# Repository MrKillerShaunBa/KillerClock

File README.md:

# KillerClock

This is a Nixie tube-inspired clock made using LED filaments. These filaments are strings of micro-LEDs which imitate the look of a tungsten filament. It uses ESP-32, which syncs time with an NTP server using the on-board wifi. It uses a MAX7219 ic to run the 7 segments. Everything is powered using a 5V 2A wall adaptor. There are also Glass test tubes to match the look of a Nixie tube.

I got the inspiration when I chanced upon a [Nixie tube clock](https://nixieshop.com/), which I found very interesting. Since Nixie tubes aren't available reliably in India, I made one using LEDs.

## CAD

## PCB

# BOM
| Product | Quantity (MOQ) | Source | Total Price(INR)(includes tax) | Price($)(Converted) | Link |
| :-----: | :-----: | :-----: | :-----: | :-----: | :-----: |
| MAX7219 8-Digit LED Display Driver IC | 2 | eBhoot | 225 | 2.60 | [here](https://ebhoot.in/shop-2/ics/driver-interface-ic/max7219-8-digit-led-display-driver-ic/) |
| DC Power Jack Female | 2 | eBhoot | 14.6 | 0.17 | [here](https://ebhoot.in/shop-2/connectors/dc-005-dc-power-jack-female-adapter-pcb-mount-2-1-x-5-5mm/) |
| ESP32 Development Board | 1 | eBhoot | 377.6 | 4.37 | [here](https://ebhoot.in/shop-2/esp-wifi-boards/esp32-development-board-type-c-usb-ch340c-wifi-bluetooth-ultra-low-power-dual-core/) |
| 10uF 25V Electrolytic Capacitor | 3 | eBhoot | 5.31 | 0.061 | [here](https://ebhoot.in/shop-2/electronics-components/capacitors/10uf-25v-electrolytic-capacitor/) |
| 0.1uF Ceramic Capacitor | 5 | eBhoot | 5.3 | 0.061 | [here](https://ebhoot.in/shop-2/electronics-components/capacitors/0-1uf-104-ceramic-capacitor/) |
| 10K Ohm Resistor | 10 | eBhoot | 5.9 | 0.068 | [here](https://ebhoot.in/shop-2/electronics-components/resistors/10k-ohm-0-25watt-carbon-film-resistor/) |
| 5v-2A DC adaptor | 1 | eBhoot | 123.9 | 1.43 | [here](https://ebhoot.in/shop-2/power-supply/adapters/5v-2a-dc-adapter-with-led-dual-pin-dc/) |
| Ebhoot Shipping | ~ | eBhoot | 90 | 1.04 | ~ |
| 40×2 Pin Male Berg Strip | 2 | Sharvi | 28.91 | 0.33 | [here](https://sharvielectronics.com/product/40x2-pin-male-berg-strip-break-away-header-right-angle-2-54mm-pitch/) |
| 40x1 Pin Male Berg Strip | 1 | Sharvi | 6.8 | 0.079 | [here](https://sharvielectronics.com/product/40x1-pin-male-10mm-height-berg-header-straight-2-54mm-pitch/) |
| 40x1 Pin Female Berg Strip | 1 | Sharvi | 9.7 | 0.11 | [here](https://sharvielectronics.com/product/40x1-pin-female-berg-strip-break-away-header-straight-2-54mm-pitch/) |
| 2x4 pin female berg strip | 5 | Sharvi | 49.7 | 0.57 | [here](https://sharvielectronics.com/product/2x4-8pin-female-berg-strip-break-away-header-straight-2-54mm-pitch/) |
| 24 Pin IC Base | 5 | Sharvi | 29.3 | 0.34 | [here](https://sharvielectronics.com/product/24-pin-ic-base-for-dip-24-package/) |
| M2x6mm Allen bolt | 10 | Sharvi | 112.7 | 1.30 | [here](https://sharvielectronics.com/product/m2x6mm-allen-socket-head-cap-bolt-mild-carbon-steel/) |
| M2x20mm Allen Bolt | 10 | Sharvi | 163.5 | 1.89 | [here](https://sharvielectronics.com/product/m2x20mm-allen-socket-head-cap-bolt-mild-carbon-steel/) |
| M2X3mm Brass Heat Insert | 10 | Sharvi | 33.7 | 0.39 | [here](https://sharvielectronics.com/product/m2x3-mm-brass-heat-set-threaded-round-insert-nut/) |
| Sharvi Shipping | ~ | Sharvi | 75 | 0.87 | ~ |
| LED Filament 3V 26mm | 11*3 | Adafruit | ~ | 54.34 | [here](https://www.adafruit.com/product/5505) (Not available in this size anywhere in India; Inclues tax and shipping) |
| 38x200mm test tubes | 12 | Amazon | 990 | 11.45 | [here](https://amzn.in/d/gJka92f) |
| 10x75mm test tubes | 6 | Amazon | 179 | 2.04 | [here](https://amzn.in/d/571r95v) |
| PCB | 5 | JLC PCB | | 20 | Used coupon and includes shipping | 
| Case | 1 | Print Legion | | ~5 | Only Shipping |

Total Cost- $115-120

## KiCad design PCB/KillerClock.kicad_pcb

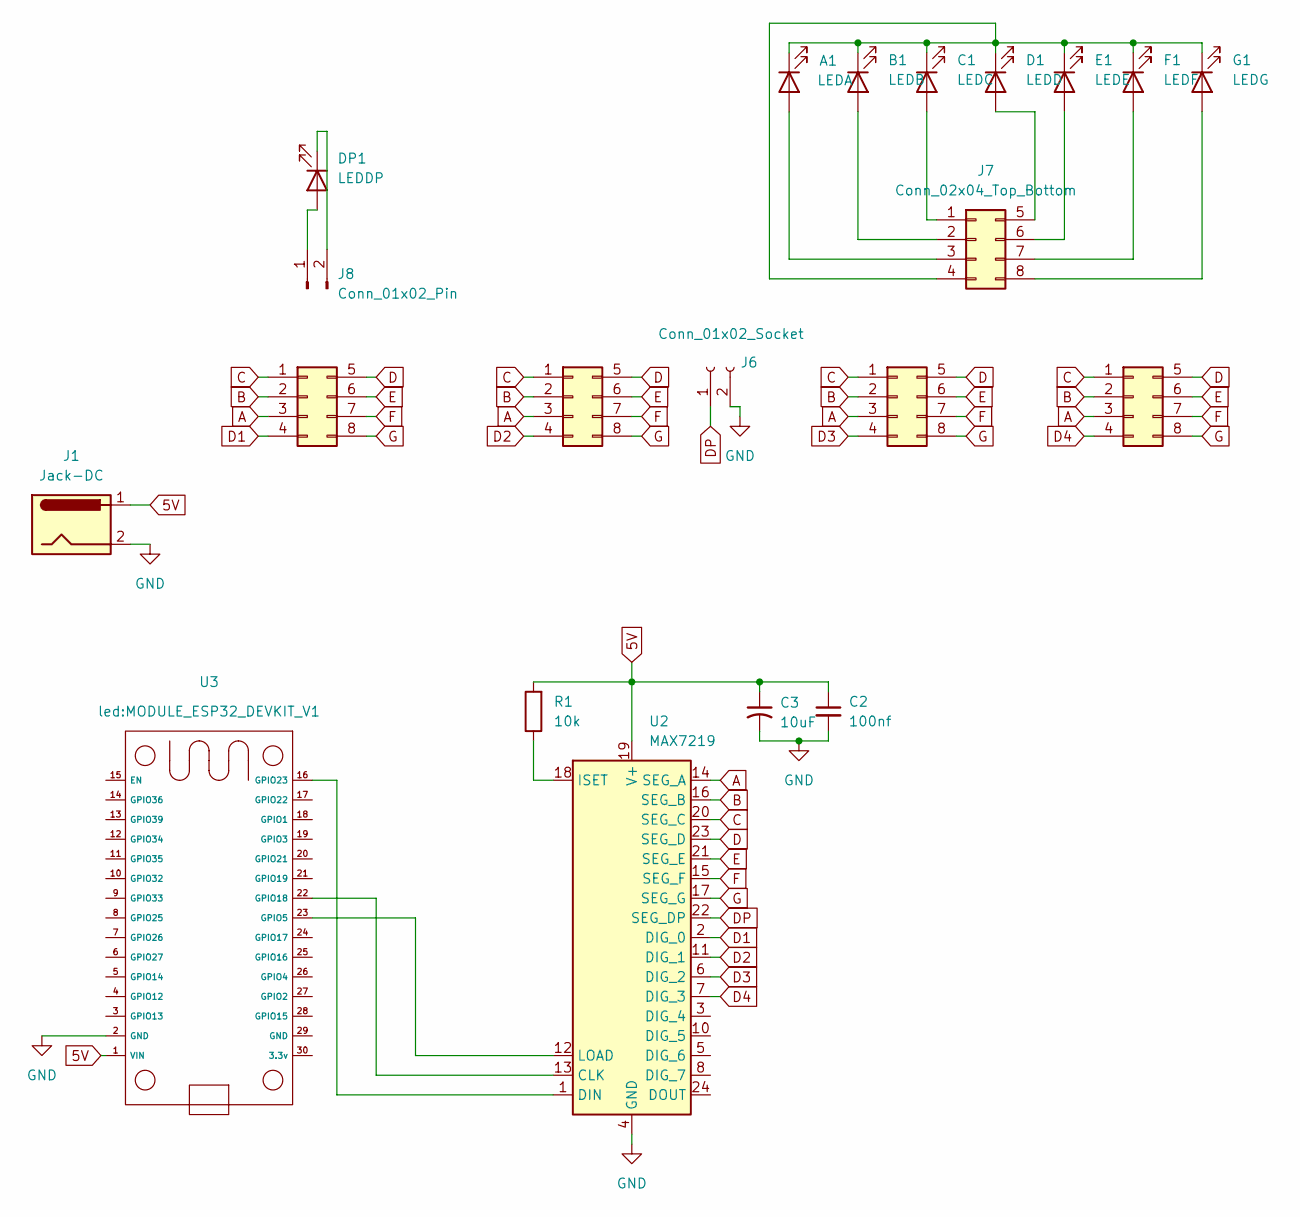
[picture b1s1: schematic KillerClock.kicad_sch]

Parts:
A1: LEDA; 7SEG
B1: LEDB; 7SEG
C1: LEDC; 7SEG
C2: 100nf; C_Disc_D5.0mm_W2.5mm_P5.00mm
C3: 10uF; CP_Radial_D5.0mm_P2.50mm
D1: LEDD; 7SEG
DP1: LEDDP; 7SEG
E1: LEDE; 7SEG
F1: LEDF; 7SEG
G1: LEDG; 7SEG
J1: Jack-DC; BarrelJack_Horizontal
J2, J3, J4, J5: Conn_02x04_Top_Bottom; PinHeader_2x04_P2.54mm_Vertical
J6: Conn_01x02_Socket; PinHeader_1x02_P2.54mm_Vertical
J7: Conn_02x04_Top_Bottom; PinHeader_2x04_P2.54mm_Horizontal
J8: Conn_01x02_Pin; PinHeader_1x02_P2.54mm_Horizontal
R1: 10k; R_Axial_DIN0207_L6.3mm_D2.5mm_P10.16mm_Horizontal
U2: MAX7219; DIP-24_W7.62mm_Socket
U3: MODULE_ESP32_DEVKIT_V1

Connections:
5V: C2.1, C3.1, J1.1, R1.2, U2.19 (V+), U3.1 (VIN)
A: J2.3, J3.3, J4.3, J5.3, U2.14 (SEG_A)
B: J2.2, J3.2, J4.2, J5.2, U2.16 (SEG_B)
C: J2.1, J3.1, J4.1, J5.1, U2.20 (SEG_C)
D: J2.5, J3.5, J4.5, J5.5, U2.23 (SEG_D)
D1: J2.4, U2.2 (DIG_0)
D2: J3.4, U2.11 (DIG_1)
D3: J4.4, U2.6 (DIG_2)
D4: J5.4, U2.7 (DIG_3)
DP: J6.1, U2.22 (SEG_DP)
E: J2.6, J3.6, J4.6, J5.6, U2.21 (SEG_E)
F: J2.7, J3.7, J4.7, J5.7, U2.15 (SEG_F)
G: J2.8, J3.8, J4.8, J5.8, U2.17 (SEG_G)
GND: C2.2, C3.2, J1.2, J6.2, U2.4 (GND), U2.9 (GND), U3.2 (GND)
unnamed: A1.2 (A), J7.3
unnamed: A1.1 (K), B1.1 (K), C1.1 (K), D1.1 (K), E1.1 (K), F1.1 (K), G1.1 (K), J7.4
unnamed: B1.2 (A), J7.2
unnamed: C1.2 (A), J7.1
unnamed: D1.2 (A), J7.5
unnamed: DP1.2 (A), J8.1
unnamed: DP1.1 (K), J8.2
unnamed: E1.2 (A), J7.6
unnamed: F1.2 (A), J7.7
unnamed: G1.2 (A), J7.8
unnamed: U2.13 (CLK), U3.22 (GPIO18)
unnamed: U2.1 (DIN), U3.16 (GPIO23)
unnamed: R1.1, U2.18 (ISET)
unnamed: U2.12 (LOAD), U3.23 (GPIO5)

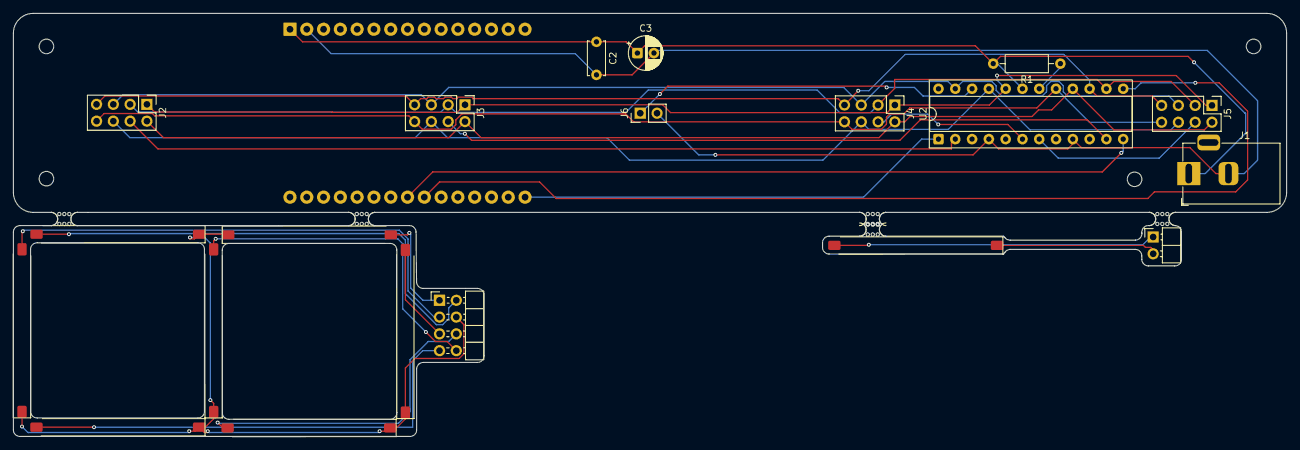
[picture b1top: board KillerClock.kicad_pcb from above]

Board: 2 copper layers, 192.6 x 64.0 mm, 26 parts (1 on the bottom side), 28 nets.

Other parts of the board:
mouse-bite-2mm-slot, mouse-bite-2mm-slot#2, mouse-bite-2mm-slot#3, mouse-bite-2mm-slot#4, mouse-bite-2mm-slot#5: VAL**; mouse-bite-2mm-slot
